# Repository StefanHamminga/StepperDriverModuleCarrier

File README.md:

# StepperDriverModuleCarrier

RP2040 based carrier board for 4 TMC2209 stepper motor driver module boards (as used in 3D printer controllers)

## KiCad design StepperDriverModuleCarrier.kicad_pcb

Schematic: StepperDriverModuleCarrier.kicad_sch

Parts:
A1, A2, A3, A4: Makerbase MKS TMC2209 v2.0; BigTreeTech_TMC2209_v1.2
C1, C8, C9, C14, C16, C18, C20, C21, C22, C25, C26, C27, C29, C31, C32, C33, C34, C35, C36, C37, C38: 0.1uF; 1005_C; Voltage 50V; Tolerance 10%; MPN CL05B104KO5NNNC; JLCPCB Part C1525
C2, C5: 27pF C0G 50V; 1005_C; Voltage 50V; Tolerance 10%; MPN 0402CG270J500NT; JLCPCB Part C1557
C3, C6, C10, C11, C12, C19, C28: 1uF; 2012_C; Voltage 50V; Tolerance 10%; MPN CL21B105KBFNNNE; JLCPCB Part C28323
C4, C23, C24, C30, C40: 10uF; 1005_C; Voltage 6.3V; Tolerance 10%; MPN CL05A106MQ5NUNC; JLCPCB Part C15525
C7, C13, C15, C17: 47uF 35V; CP_Radial_D5.0mm_P2.00mm; MPN RG035M470LO5*11TA-1A1E; JLCPCB Part C357615
C39, C41, C42: 100uF 35V; CP_Radial_D8.0mm_P3.50mm; MPN NPHDD1H101MF; JLCPCB Part C269987
D1: 40V 5A 550mV; DO-214AC_KA; MPN SS54; JLCPCB Part C22452
D2: PWR; 1608_C_KA; MPN 19-217/GHC-YR1S2/3T; JLCPCB Part C72043
FD1, FD2, FD3: FIDUCIAL_MARKER; ToolingHole_JLCPCB_1.152mm; MPN DNP
H1, H2, H3, H4: MOUNT_HOLE; MountingHole_3.2mm_M3_ISO7380_Pad_TopOnly; MPN DNP
J1: GPIO; PinHeader_2x12_P2.54mm_Vertical; MPN PZ254V-12-24P; JLCPCB Part C492429
J2: Vin; Ningbo_Kangnex_Electric_WJ126V-5.0-2P; MPN WJ126V-5.0-2P; JLCPCB Part C8404
J3, J4, J5, J6, J7, J8, J9, J10: MODHEADER; Dummy_01x08_2.54mm_header; MPN C27438; JLCPCB Part C27438
JP1: CLKSYNC; SolderJumper-3_P1.3mm_Bridged12_RoundedPad1.0x1.5mm_NumberL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; MPN DNP
JP2, JP4, JP6, JP8: MS1; SolderJumper-3_P1.3mm_Bridged12_RoundedPad1.0x1.5mm_NumberL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; MPN DNP
JP3, JP5, JP7, JP9: MS2; SolderJumper-3_P1.3mm_Bridged12_RoundedPad1.0x1.5mm_NumberL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; MPN DNP
JP10, JP11, JP12, JP13: SER; SolderJumper-3_P1.3mm_Bridged12_RoundedPad1.0x1.5mm_NumberL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; MPN DNP
M1, M2, M3, M4: Bipolar_Stepper_Motor_A1A2B2B1; JST_XH_B4B-XH-A_1x04_P2.50mm_Vertical; MPN XH-4A; JLCPCB Part C57846
R1, R4, R8, R19, R20, R21, R22, R23: 1k; 1005_C; MPN 0402WGF1001TCE; JLCPCB Part C11702
R2, R3: 22; 1005_C; MPN 0402WGF220JTCE; JLCPCB Part C25092
R5: 100k; 1005_C; MPN 0402WGF1003TCE; JLCPCB Part C25741
R6, R7, R9, R10, R11, R12, R13, R14, R15, R16, R17, R18: 10k; 1005_C; MPN 0402WGF1002TCE; JLCPCB Part C25744
R24, R25, R26, R27: 0; 1005_C; MPN 0402WGF0000TCE; JLCPCB Part C17168
U1: RP2040; QFN-56-1EP_7x7mm_P0.4mm_EP3.2x3.2mm; MPN RP2040; JLCPCB Part C2040
U2: W25Q128JVS; SOIC-8_5.23x5.23mm_P1.27mm; MPN W25Q128JVSIQ; JLCPCB Part C97521
U3: XC6206P332MR; SOT-23; MPN XC6206P332MR; JLCPCB Part C5446
Y1: 12MHz; Crystal_SMD_3225-4Pin_3.2x2.5mm; MPN X322512MSB4SI; JLCPCB Part C9002

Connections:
+1V1: C1.1, C4.1, C9.1, U1.23 (DVDD), U1.45 (VREG_VOUT), U1.50 (DVDD)
+3V3: A1.1 (EN), A1.10 (VIO), A2.1 (EN), A2.10 (VIO), A3.1 (EN), A3.10 (VIO), A4.1 (EN), A4.10 (VIO), C8.1, C14.1, C16.1, C18.1, C20.1, C21.1, C22.1, C23.1, C24.1, C29.1, C30.1, C31.1, C32.1, C33.1, C34.1, C35.1, C36.1, C37.1, C38.1, C40.1, JP2.3, JP3.3, JP4.3, JP5.3, JP6.3, JP7.3, JP8.3, JP9.3, R1.2, R7.1, R9.2, R10.1, U1.1 (IOVDD), U1.10 (IOVDD), U1.22 (IOVDD), U1.33 (IOVDD), U1.42 (IOVDD), U1.43 (ADC_AVDD), U1.44 (VREG_VIN), U1.48 (USB_VDD), U1.49 (IOVDD), U2.8 (VCC), U3.2 (VO)
+5V: C19.1, C28.1, D1.A (2), J1.24, R23.1, U3.3 (VI)
/stepper_clk: JP1.1, U1.36 (GPIO24)
DIAG1: A1.17 (DIAG), U1.30 (GPIO19)
DIAG2: A2.17 (DIAG), U1.15 (GPIO12)
DIAG3: A3.17 (DIAG), U1.28 (GPIO17)
DIAG4: A4.17 (DIAG), U1.17 (GPIO14)
DIR1: A1.8 (DIR), U1.2 (GPIO0)
DIR2: A2.8 (DIR), U1.5 (GPIO3)
DIR3: A3.8 (DIR), U1.6 (GPIO4)
DIR4: A4.8 (DIR), U1.9 (GPIO7)
DRV_CLK: A1.6 (CLK), A2.6 (CLK), A3.6 (CLK), A4.6 (CLK), JP1.2
ESTOP1: J1.2, U1.31 (GPIO20)
ESTOP2: J1.4, U1.32 (GPIO21)
ESTOP3: J1.6, U1.34 (GPIO22)
ESTOP4: J1.8, U1.35 (GPIO23)
GND: A1.9 (GND), A1.15 (GND), A2.9 (GND), A2.15 (GND), A3.9 (GND), A3.15 (GND), A4.9 (GND), A4.15 (GND), C1.2, C2.2, C3.2, C4.2, C5.2, C6.2, C7.2 (-), C8.2, C9.2, C10.2, C11.2, C12.2, C13.2 (-), C14.2, C15.2 (-), C16.2, C17.2 (-), C18.2, C19.2, C20.2, C21.2, C22.2, C23.2, C24.2, C25.2, C26.1, C27.1, C28.2, C29.2, C30.2, C31.2, C32.2, C33.2, C34.2, C35.2, C36.2, C37.2, C38.2, C39.2 (-), C40.2, C41.2 (-), C42.2 (-), D2.K (1), H1.1, H2.1, H3.1, H4.1, J1.1, J1.3, J1.5, J1.7, J1.9, J1.11, J1.13, J1.15, J1.23, J2.2, JP1.3, JP2.1, JP3.1, JP4.1, JP5.1, JP6.1, JP7.1, JP8.1, JP9.1, R6.2, U1.19 (TESTEN), U1.57 (GND), U2.4 (GND), U3.1 (GND), Y1.2 (GND), Y1.4 (GND)
HEAT1: J1.14, U1.37 (GPIO25)
HEAT2: J1.16, U1.38 (GPIO26/ADC0)
INDEX1: A1.19 (INDEX), U1.29 (GPIO18)
INDEX2: A2.19 (INDEX), U1.16 (GPIO13)
INDEX3: A3.19 (INDEX), U1.27 (GPIO16)
INDEX4: A4.19 (INDEX), U1.18 (GPIO15)
MEAS_TEMP1: C26.2, J1.10, R7.2, U1.39 (GPIO27/ADC1)
MEAS_TEMP2: C27.2, J1.12, R10.2, U1.40 (GPIO28/ADC2)
MEAS_VM: C25.1, R5.2, R6.1, U1.41 (GPIO29/ADC3)
unnamed: A1.2 (MS1), R11.2
unnamed: A1.3 (MS2), R12.2
unnamed: A1.4 (PDN/UART), R24.2
unnamed: A1.5 (UART), R19.2
unnamed: A1.11 (OB2), M1.4 (B1)
unnamed: A1.12 (OB1), M1.3 (B2)
unnamed: A1.13 (OA1), M1.2 (A2)
unnamed: A1.14 (OA2), M1.1 (A1)
unnamed: A2.4 (PDN/UART), R25.2
unnamed: A2.5 (UART), R20.2
unnamed: A2.11 (OB2), M2.4 (B1)
unnamed: A2.12 (OB1), M2.3 (B2)
unnamed: A2.13 (OA1), M2.2 (A2)
unnamed: A2.14 (OA2), M2.1 (A1)
unnamed: A3.2 (MS1), R15.2
unnamed: A3.3 (MS2), R16.2
unnamed: A3.4 (PDN/UART), R26.2
unnamed: A3.5 (UART), R21.2
unnamed: A3.11 (OB2), M3.4 (B1)
unnamed: A3.12 (OB1), M3.3 (B2)
unnamed: A3.13 (OA1), M3.2 (A2)
unnamed: A3.14 (OA2), M3.1 (A1)
unnamed: A4.2 (MS1), R17.2
unnamed: A4.3 (MS2), R18.2
unnamed: A4.4 (PDN/UART), R27.2
unnamed: A4.5 (UART), R22.2
unnamed: A4.11 (OB2), M4.4 (B1)
unnamed: A4.12 (OB1), M4.3 (B2)
unnamed: A4.13 (OA1), M4.2 (A2)
unnamed: A4.14 (OA2), M4.1 (A1)
unnamed: C2.1, U1.20 (XIN), Y1.1
unnamed: C5.1, R4.2, Y1.3
unnamed: D2.A (2), R23.2
unnamed: JP2.2, R11.1
unnamed: JP3.2, R12.1
unnamed: JP4.2, R13.1
unnamed: JP5.2, R14.1
unnamed: JP6.2, R15.1
unnamed: JP7.2, R16.1
unnamed: JP8.2, R17.1
unnamed: JP9.2, R18.1
unnamed: JP11.3, R20.1
unnamed: R2.1, U1.46 (USB_DM)
unnamed: R3.1, U1.47 (USB_DP)
unnamed: R4.1, U1.21 (XOUT)
unnamed: R8.2, U1.52 (QSPI_SCLK), U2.6 (CLK)
unnamed: R9.1, U1.56 (QSPI_SS_N), U2.1 (~CS)
unnamed: A2.2 (MS1), R13.2
unnamed: A2.3 (MS2), R14.2
unnamed: JP10.3, R19.1
unnamed: JP12.3, R21.1
unnamed: JP13.3, R22.1
unnamed: JP10.1, R24.1
unnamed: JP11.1, R25.1
unnamed: JP12.1, R26.1
unnamed: JP13.1, R27.1
unnamed: U1.51 (QSPI_SD3), U2.7 (IO3)
unnamed: U1.53 (QSPI_SD0), U2.5 (DI(IO0))
unnamed: U1.54 (QSPI_SD2), U2.3 (IO2)
unnamed: U1.55 (QSPI_SD1), U2.2 (DO(IO1))
RESET: J1.17, R1.1, U1.26 (RUN)
SER1: JP10.2, U1.12 (GPIO9)
SER2: JP11.2, U1.11 (GPIO8)
SER3: JP12.2, U1.13 (GPIO10)
SER4: JP13.2, U1.14 (GPIO11)
STEP1: A1.7 (STEP), U1.3 (GPIO1)
STEP2: A2.7 (STEP), U1.4 (GPIO2)
STEP3: A3.7 (STEP), U1.7 (GPIO5)
STEP4: A4.7 (STEP), U1.8 (GPIO6)
SWDCLK: J1.19, U1.24 (SWDCLK)
SWDIO: J1.20, U1.25 (SWDIO)
USB+: J1.22, R3.2
USB-: J1.21, R2.2
VM: A1.16 (VM), A2.16 (VM), A3.16 (VM), A4.16 (VM), C3.1, C6.1, C7.1 (+), C10.1, C11.1, C12.1, C13.1 (+), C15.1 (+), C17.1 (+), C39.1 (+), C41.1 (+), C42.1 (+), D1.K (1), J2.1, R5.1
~USB_BOOT: J1.18, R8.1

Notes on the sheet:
JLC tooling holes

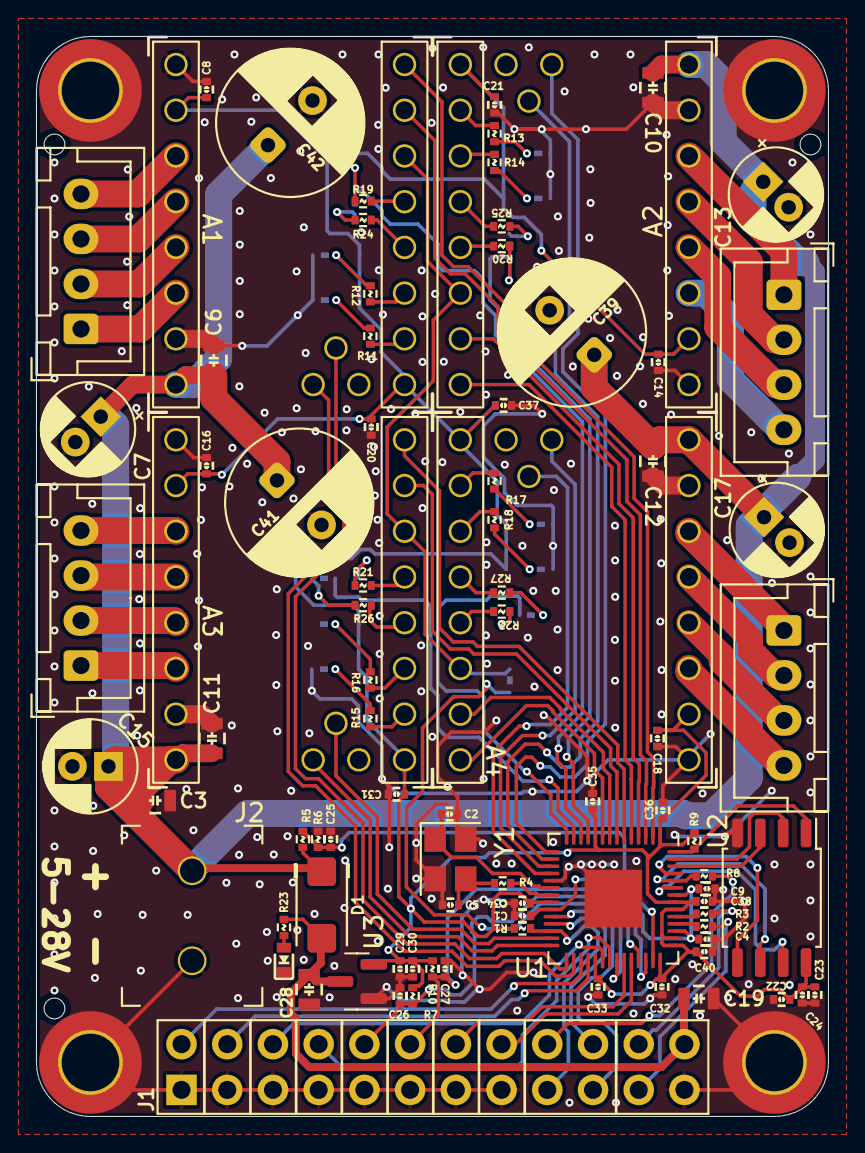
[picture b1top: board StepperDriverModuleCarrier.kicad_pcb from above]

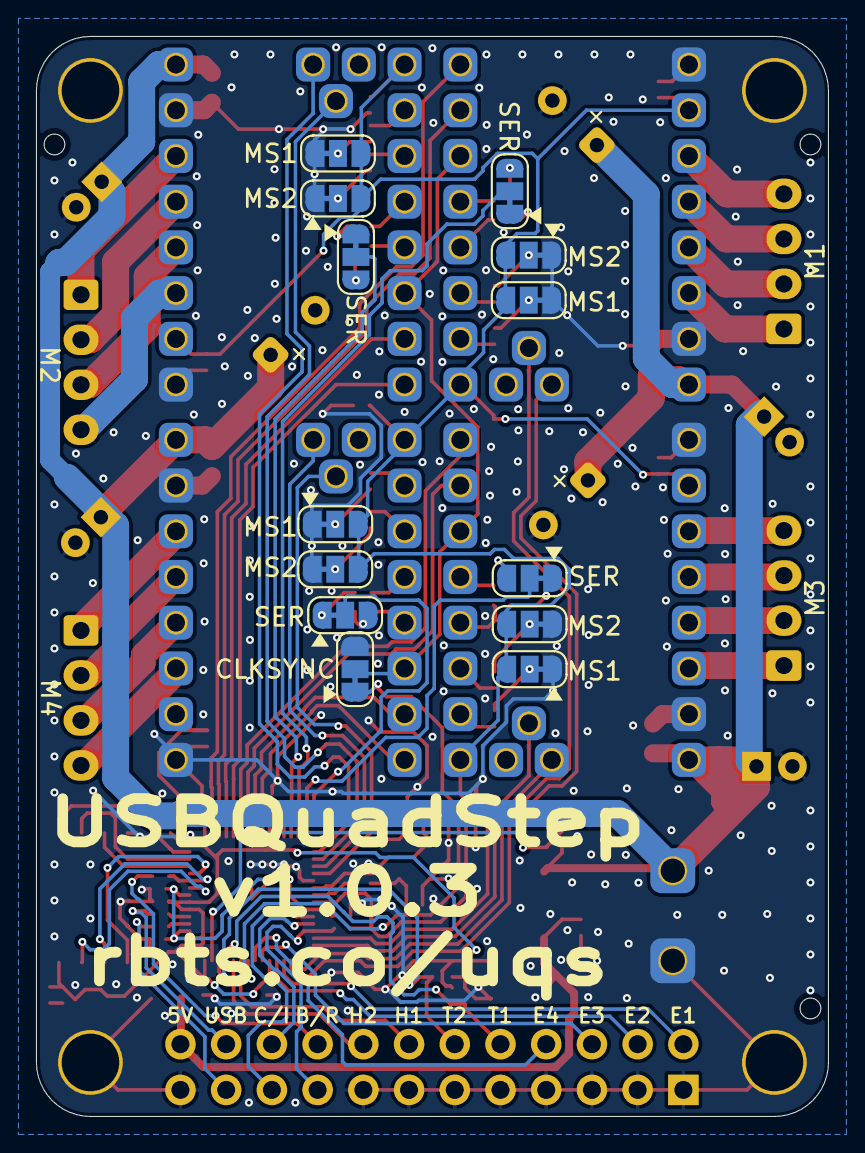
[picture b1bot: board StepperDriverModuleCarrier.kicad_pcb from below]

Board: 2 copper layers, 44.0 x 60.0 mm, 113 parts (13 on the bottom side), 102 nets.
